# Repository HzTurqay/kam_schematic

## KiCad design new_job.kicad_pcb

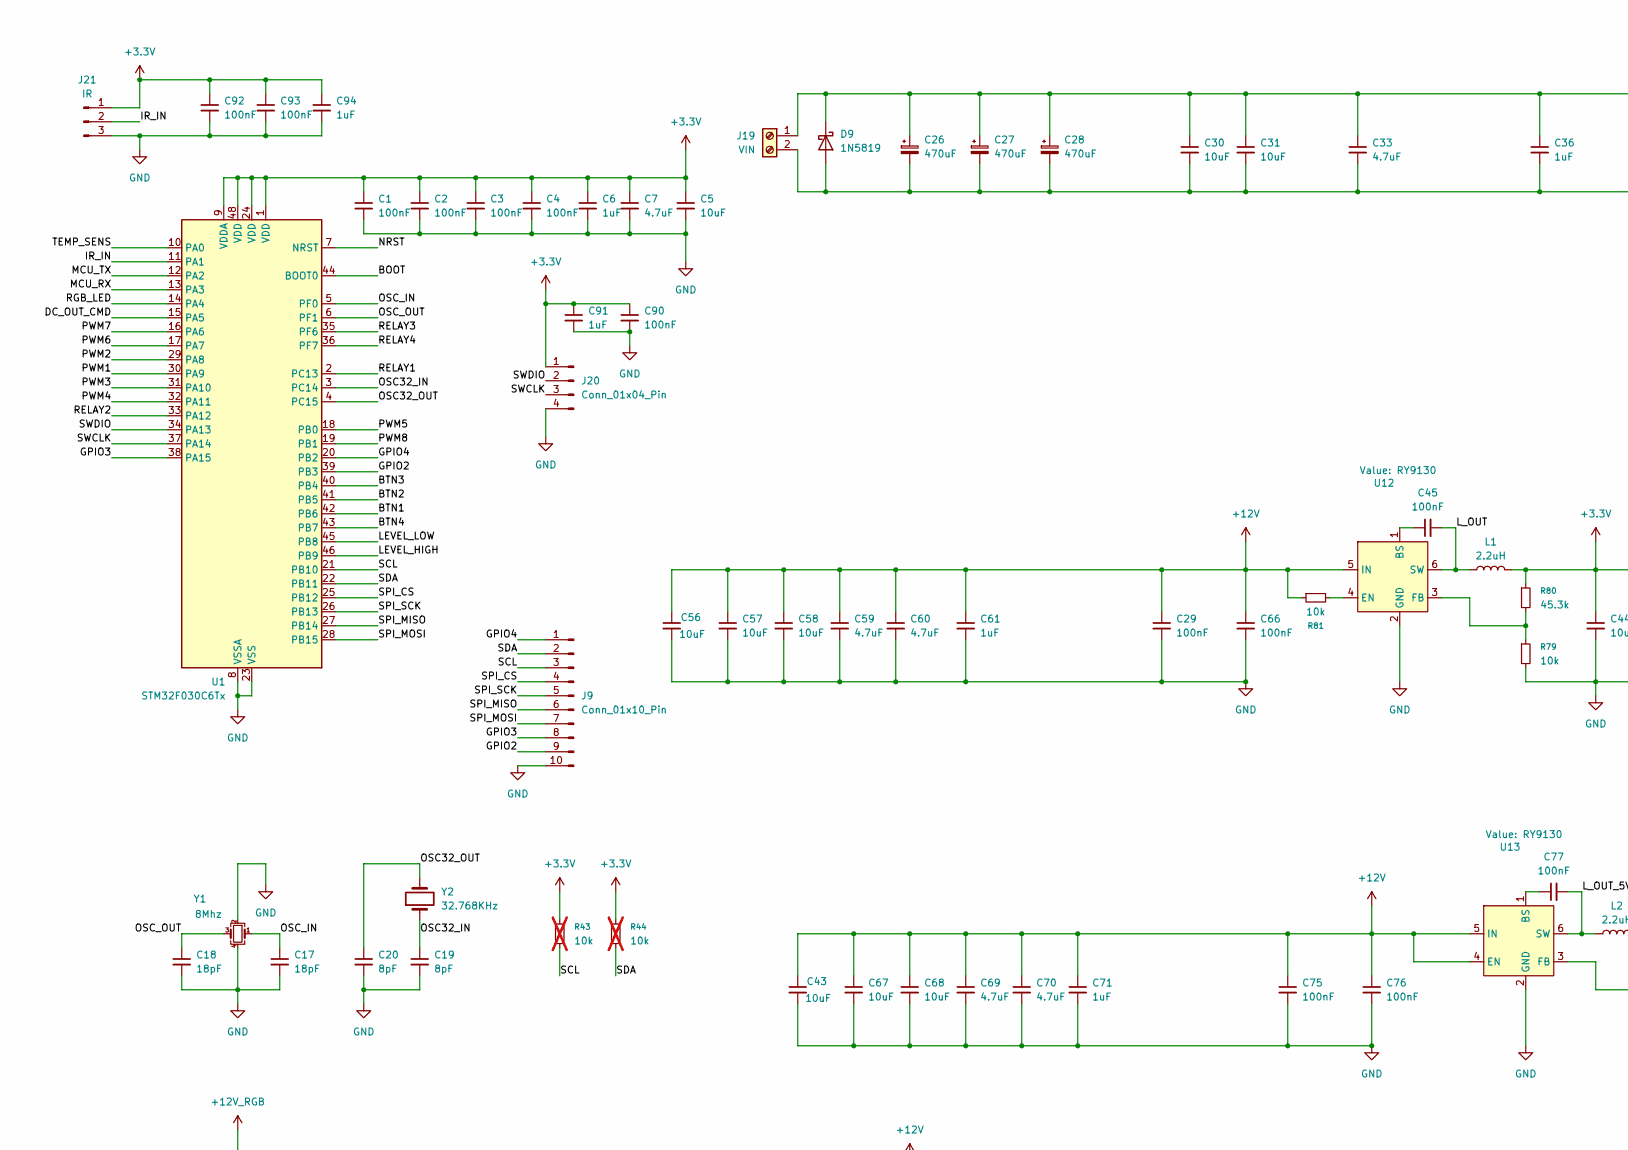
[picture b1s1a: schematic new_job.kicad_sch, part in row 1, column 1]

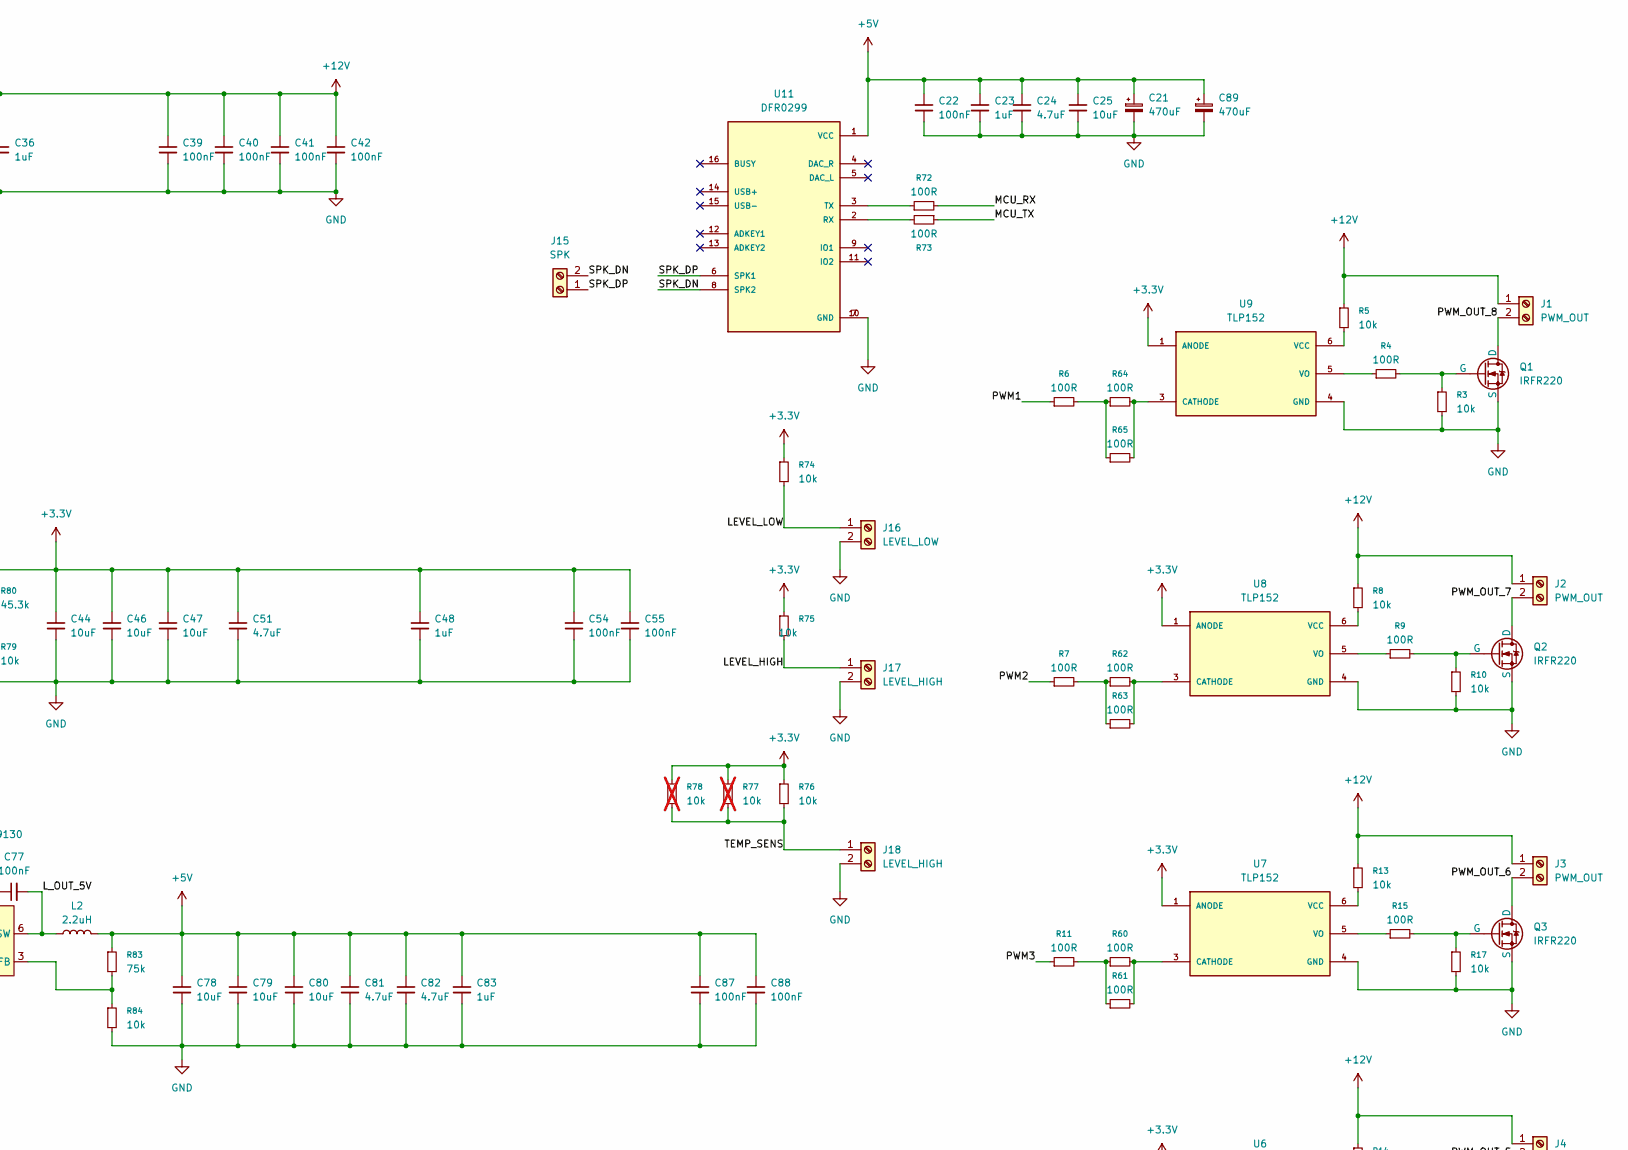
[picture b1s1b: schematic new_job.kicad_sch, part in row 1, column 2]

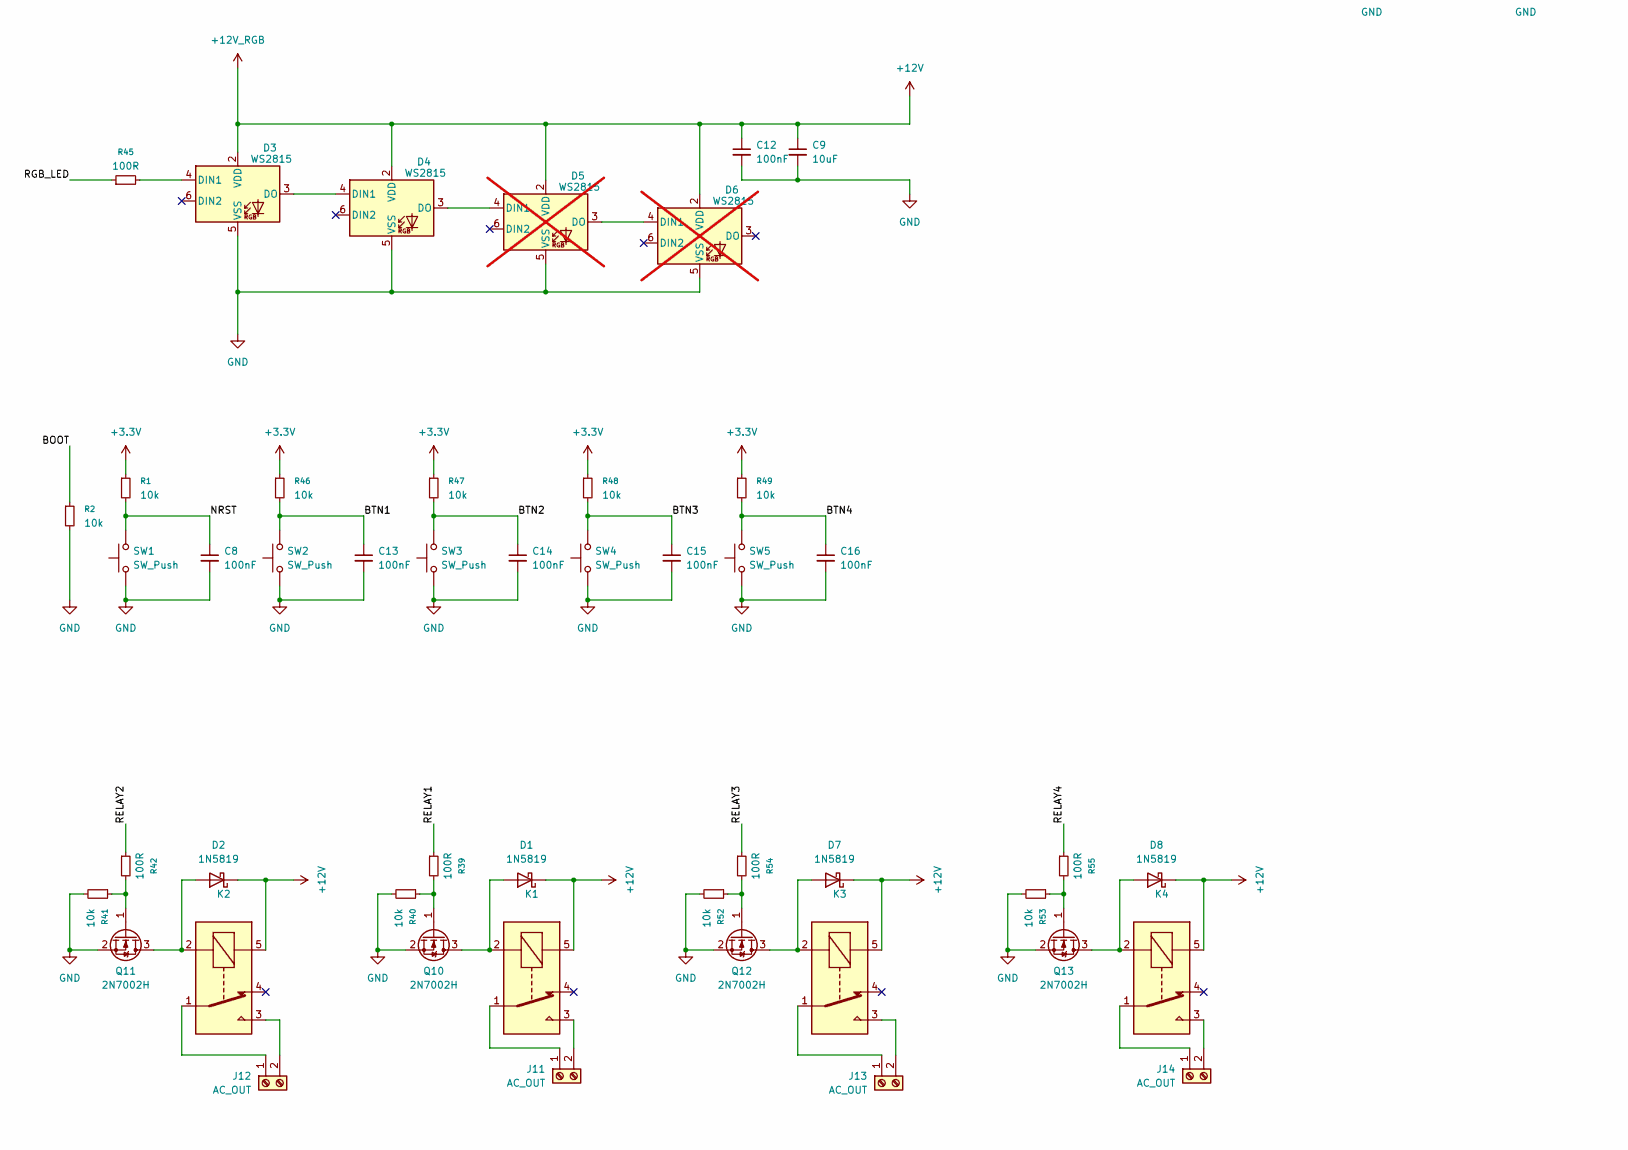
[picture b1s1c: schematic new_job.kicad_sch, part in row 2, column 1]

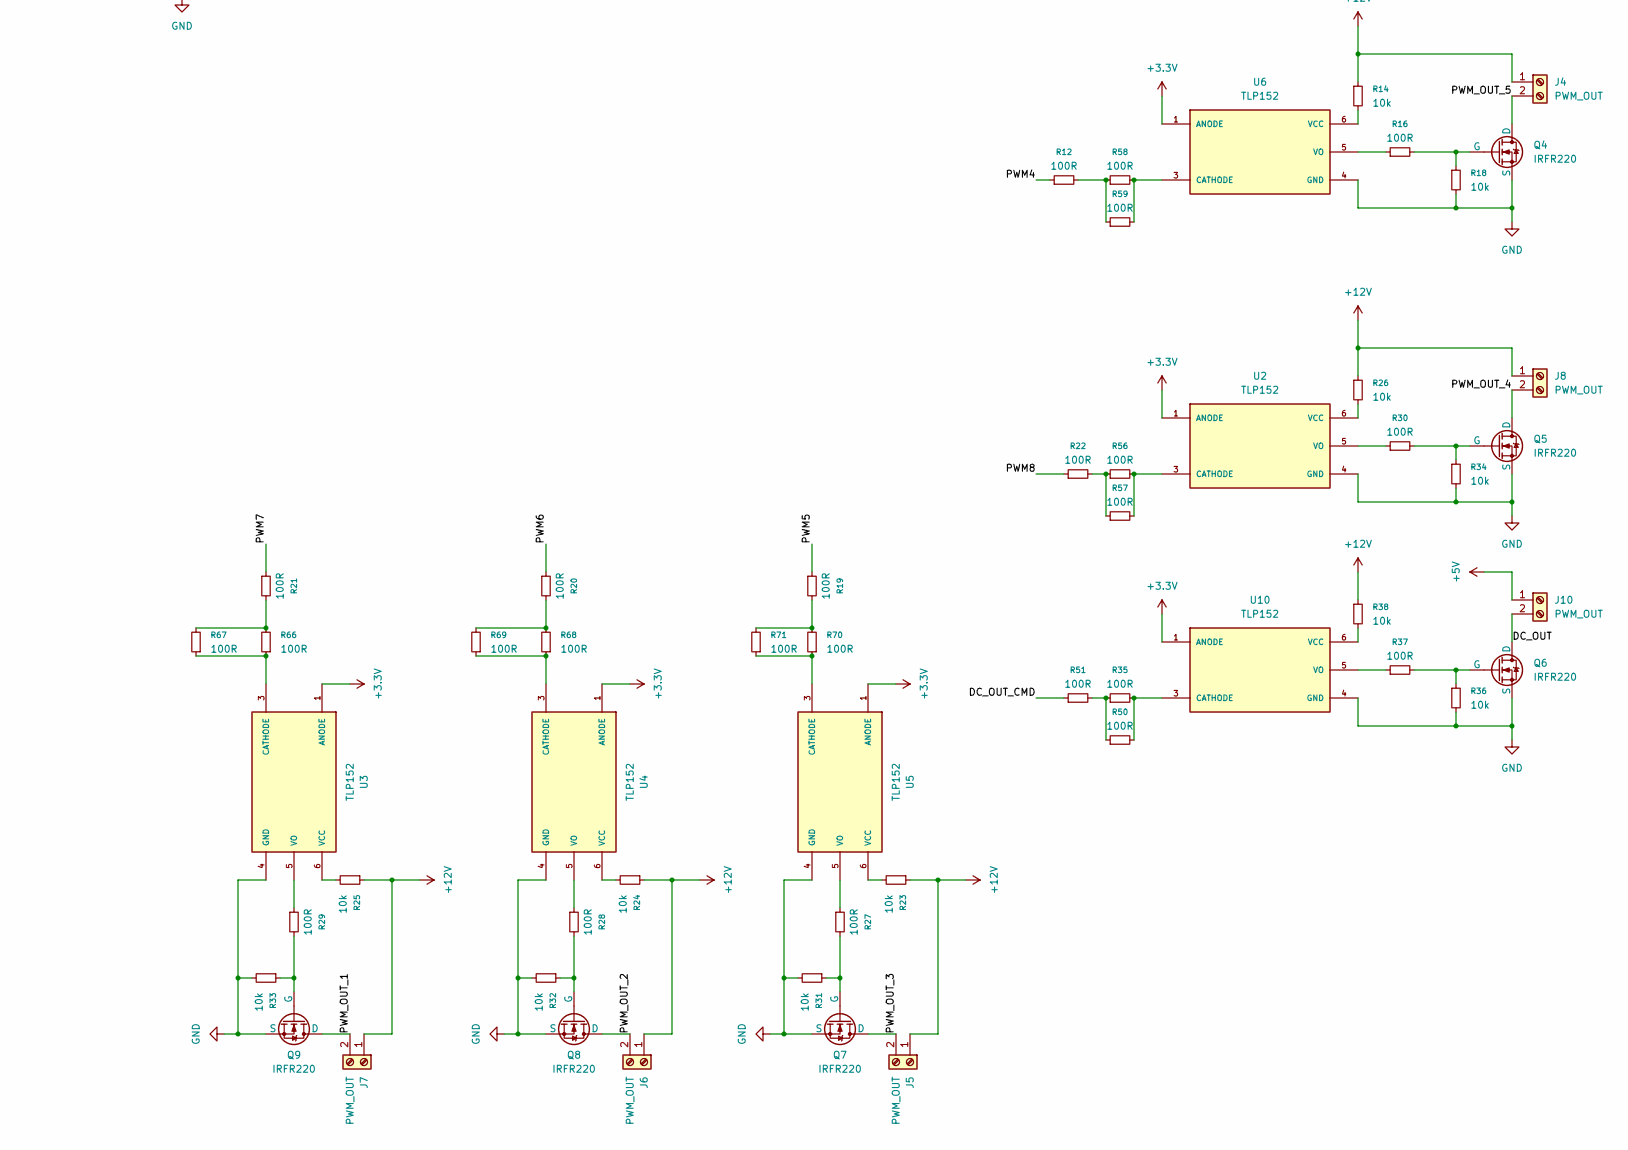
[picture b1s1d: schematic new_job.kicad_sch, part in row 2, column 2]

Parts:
C1, C2, C3, C4, C8, C12, C13, C14, C15, C16, C22, C29, C39, C40, C41, C42, C45, C54, C55, C66, C75, C76, C77, C87, C88, C90, C92, C93: 100nF; C_0402_1005Metric; LCSC Part C328914
C5, C9, C25, C30, C31, C43, C44, C46, C47, C56, C57, C58, C67, C68, C78, C79, C80: 10uF; C_0805_2012Metric; LCSC Part C5137476
C6, C23, C36, C48, C61, C71, C83, C91, C94: 1uF; C_0402_1005Metric; LCSC Part C6119792
C7, C24, C33, C51, C59, C60, C69, C70, C81, C82: 4.7uF; C_0603_1608Metric; LCSC Part C6119855
C17, C18: 18pF; C_0402_1005Metric; LCSC Part C5137554
C19, C20: 8pF; C_0402_1005Metric; LCSC Part C5448809
C21, C26, C27, C28, C89: 470uF; CP_Elec_10x10.5; LCSC Part C5162362
D1, D2, D7, D8, D9: 1N5819; D_SOD-123; LCSC Part C5451628
D3, D4: WS2815; LED_WS2812_PLCC6_5.0x5.0mm_P1.6mm; LCSC Part C19188610
D5, D6: WS2815; LED_WS2812_PLCC6_5.0x5.0mm_P1.6mm; LCSC Part C19188610; not fitted
J1, J2, J3, J4, J5, J6, J7, J8, J10: PWM_OUT; Molex_SL_171971-0002_1x02_P2.54mm_Vertical
J9: Conn_01x10_Pin; PinHeader_1x10_P2.54mm_Vertical
J11, J12, J13, J14: AC_OUT; TerminalBlock_RND_205-00067_1x02_P7.50mm_Horizontal; LCSC Part C557649
J15: SPK; Molex_SL_171971-0002_1x02_P2.54mm_Vertical
J16: LEVEL_LOW; PinHeader_1x02_P2.54mm_Vertical
J17, J18: LEVEL_HIGH; PinHeader_1x02_P2.54mm_Vertical
J19: VIN; Molex_SL_171971-0002_1x02_P2.54mm_Vertical
J20: Conn_01x04_Pin; PinHeader_1x04_P2.54mm_Vertical
J21: IR; PinHeader_1x03_P2.54mm_Vertical
K1, K2, K4: SANYOU_SRD_Form_C; Relay_SPDT_SANYOU_SRD_Series_Form_C; LCSC Part C30431
K3: SANYOU_SRD_Form_C; Relay_SPDT_SANYOU_SRD_Series_Form_C
L1, L2: 2.2uH; L_APV_ANR4010; LCSC Part C431273
Q1, Q2, Q3, Q4, Q5, Q6, Q7, Q8, Q9: IRFR220; TO-252-2; LCSC Part C2584
Q10, Q11, Q12, Q13: 2N7002H; SOT-23; LCSC Part C8545
R1, R2, R3, R5, R8, R10, R13, R14, R17, R18, R23, R24, R25, R26, R31, R32, R33, R34, R36, R38, R40, R41, R46, R47, R48, R49, R52, R53, R74, R75, R76, R79, R81, R84: 10k; R_0402_1005Metric; LCSC Part C881063
R4, R6, R7, R9, R11, R12, R15, R16, R19, R20, R21, R22, R27, R28, R29, R30, R35, R37, R39, R42, R45, R50, R51, R54, R55, R56, R57, R58, R59, R60, R61, R62, R63, R64, R65, R66, R67, R68, R69, R70, R71, R72, R73: 100R; R_0402_1005Metric; LCSC Part C22369194
R43, R44, R77, R78: 10k; R_0402_1005Metric; LCSC Part C881063; not fitted
R80: 45.3k; R_0402_1005Metric; LCSC Part C2933099
R83: 75k; R_0402_1005Metric; LCSC Part C2906965
SW1, SW2, SW3, SW4, SW5: SW_Push; SW_SPST_B3S-1000; LCSC Part C2909692
U1: STM32F030C6Tx; LQFP-48_7x7mm_P0.5mm; LCSC Part C106925
U2, U3, U4, U5, U6, U7, U8, U9, U10: TLP152; IC_TLP152; PARTREV 6; LCSC Part C22436730
U11: DFR0299; MODULE_DFR0299
U12, U13: RY9130; SOT-23-6; LCSC Part C2981046
Y1: 8Mhz; Crystal_SMD_3225-4Pin_3.2x2.5mm; LCSC Part C2835958
Y2: 32.768KHz; Crystal_SMD_3215-2Pin_3.2x1.5mm; LCSC Part C907541

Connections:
+3.3V: C1.1, C2.1, C3.1, C4.1, C5.1, C6.1, C7.1, C44.1, C46.1, C47.1, C48.1, C51.1, C54.1, C55.1, C90.1, C91.1, C92.1, C93.1, C94.1, J20.1, J21.1, L1.2, R1.1, R43.1, R44.1, R46.1, R47.1, R48.1, R49.1, R74.1, R75.1, R76.1, R77.1, R78.1, R80.1, U1.1 (VDD), U1.9 (VDDA), U1.24 (VDD), U1.48 (VDD), U2.1 (ANODE), U3.1 (ANODE), U4.1 (ANODE), U5.1 (ANODE), U6.1 (ANODE), U7.1 (ANODE), U8.1 (ANODE), U9.1 (ANODE), U10.1 (ANODE)
+5V: C21.1, C22.1, C23.1, C24.1, C25.1, C78.1, C79.1, C80.1, C81.1, C82.1, C83.1, C87.1, C88.1, C89.1, J10.1, L2.2, R83.1, U11.1 (VCC)
+12V: C9.1, C12.1, C26.1, C27.1, C28.1, C29.1, C30.1, C31.1, C33.1, C36.1, C39.1, C40.1, C41.1, C42.1, C43.1, C56.1, C57.1, C58.1, C59.1, C60.1, C61.1, C66.1, C67.1, C68.1, C69.1, C70.1, C71.1, C75.1, C76.1, D1.1 (K), D2.1 (K), D3.2 (VDD), D4.2 (VDD), D5.2 (VDD), D6.2 (VDD), D7.1 (K), D8.1 (K), D9.1 (K), J1.1, J2.1, J3.1, J4.1, J5.1, J6.1, J7.1, J8.1, J19.1, K1.5, K2.5, K3.5, K4.5, R5.1, R8.1, R13.1, R14.1, R23.1, R24.1, R25.1, R26.1, R38.1, R81.1, U12.5 (IN), U13.4 (EN), U13.5 (IN)
/BOOT: R2.1, U1.44 (BOOT0)
/BTN1: C13.1, R46.2, SW2.2, U1.42 (PB6)
/BTN2: C14.1, R47.2, SW3.2, U1.41 (PB5)
/BTN3: C15.1, R48.2, SW4.2, U1.40 (PB4)
/BTN4: C16.1, R49.2, SW5.2, U1.43 (PB7)
/DC_OUT: J10.2, Q6.2 (D)
/DC_OUT_CMD: R51.1, U1.15 (PA5)
/GPIO2: J9.9, U1.39 (PB3)
/GPIO3: J9.8, U1.38 (PA15)
/GPIO4: J9.1, U1.20 (PB2)
/IR_IN: J21.2, U1.11 (PA1)
/LEVEL_HIGH: J17.1, R75.2, U1.46 (PB9)
/LEVEL_LOW: J16.1, R74.2, U1.45 (PB8)
/L_OUT: C45.2, L1.1, U12.6 (SW)
/L_OUT_5V: C77.2, L2.1, U13.6 (SW)
/MCU_RX: R72.2, U1.13 (PA3)
/MCU_TX: R73.1, U1.12 (PA2)
/NRST: C8.1, R1.2, SW1.2, U1.7 (NRST)
/OSC32_IN: C19.1, U1.3 (PC14), Y2.1
/OSC32_OUT: C20.1, U1.4 (PC15), Y2.2
/OSC_IN: C17.1, U1.5 (PF0), Y1.1
/OSC_OUT: C18.1, U1.6 (PF1), Y1.3
/PWM1: R6.1, U1.30 (PA9)
/PWM2: R7.1, U1.29 (PA8)
/PWM3: R11.1, U1.31 (PA10)
/PWM4: R12.1, U1.32 (PA11)
/PWM5: R19.1, U1.18 (PB0)
/PWM6: R20.1, U1.17 (PA7)
/PWM7: R21.1, U1.16 (PA6)
/PWM8: R22.1, U1.19 (PB1)
/PWM_OUT_1: J7.2, Q9.2 (D)
/PWM_OUT_2: J6.2, Q8.2 (D)
/PWM_OUT_3: J5.2, Q7.2 (D)
/PWM_OUT_4: J8.2, Q5.2 (D)
/PWM_OUT_5: J4.2, Q4.2 (D)
/PWM_OUT_6: J3.2, Q3.2 (D)
/PWM_OUT_7: J2.2, Q2.2 (D)
/PWM_OUT_8: J1.2, Q1.2 (D)
/RELAY1: R39.1, U1.2 (PC13)
/RELAY2: R42.1, U1.33 (PA12)
/RELAY3: R54.1, U1.35 (PF6)
/RELAY4: R55.1, U1.36 (PF7)
/RGB_LED: R45.1, U1.14 (PA4)
/SCL: J9.3, R43.2, U1.21 (PB10)
/SDA: J9.2, R44.2, U1.22 (PB11)
/SPI_CS: J9.4, U1.25 (PB12)
/SPI_MISO: J9.6, U1.27 (PB14)
/SPI_MOSI: J9.7, U1.28 (PB15)
/SPI_SCK: J9.5, U1.26 (PB13)
/SPK_DN: J15.2, U11.8 (SPK2)
/SPK_DP: J15.1, U11.6 (SPK1)
/SWCLK: J20.3, U1.37 (PA14)
/SWDIO: J20.2, U1.34 (PA13)
/TEMP_SENS: J18.1, R76.2, R77.2, R78.2, U1.10 (PA0)
GND: C1.2, C2.2, C3.2, C4.2, C5.2, C6.2, C7.2, C8.2, C9.2, C12.2, C13.2, C14.2, C15.2, C16.2, C17.2, C18.2, C19.2, C20.2, C21.2, C22.2, C23.2, C24.2, C25.2, C26.2, C27.2, C28.2, C29.2, C30.2, C31.2, C33.2, C36.2, C39.2, C40.2, C41.2, C42.2, C43.2, C44.2, C46.2, C47.2, C48.2, C51.2, C54.2, C55.2, C56.2, C57.2, C58.2, C59.2, C60.2, C61.2, C66.2, C67.2, C68.2, C69.2, C70.2, C71.2, C75.2, C76.2, C78.2, C79.2, C80.2, C81.2, C82.2, C83.2, C87.2, C88.2, C89.2, C90.2, C91.2, C92.2, C93.2, C94.2, D3.5 (VSS), D4.5 (VSS), D5.5 (VSS), D6.5 (VSS), D9.2 (A), J9.10, J16.2, J17.2, J18.2, J19.2, J20.4, J21.3, Q1.3 (S), Q2.3 (S), Q3.3 (S), Q4.3 (S), Q5.3 (S), Q6.3 (S), Q7.3 (S), Q8.3 (S), Q9.3 (S), Q10.2 (S), Q11.2 (S), Q12.2 (S), Q13.2 (S), R2.2, R3.2, R10.2, R17.2, R18.2, R31.2, R32.2, R33.2, R34.2, R36.2, R40.2, R41.2, R52.2, R53.2, R79.2, R84.2, SW1.1, SW2.1, SW3.1, SW4.1, SW5.1, U1.8 (VSSA), U1.23 (VSS), U1.47 (VSS), U2.4 (GND), U3.4 (GND), U4.4 (GND), U5.4 (GND), U6.4 (GND), U7.4 (GND), U8.4 (GND), U9.4 (GND), U10.4 (GND), U11.7 (GND), U11.10 (GND), U12.2 (GND), U13.2 (GND), Y1.2, Y1.4
unnamed: D1.2 (A), K1.2, Q10.3 (D)
unnamed: D2.2 (A), K2.2, Q11.3 (D)
unnamed: D3.4 (DIN1), R45.2
unnamed: D3.3 (DO), D4.4 (DIN1)
unnamed: D4.3 (DO), D5.4 (DIN1)
unnamed: D5.3 (DO), D6.4 (DIN1)
unnamed: D7.2 (A), K3.2, Q12.3 (D)
unnamed: D8.2 (A), K4.2, Q13.3 (D)
unnamed: J11.1, K1.1
unnamed: J11.2, K1.3
unnamed: J12.1, K2.1
unnamed: J12.2, K2.3
unnamed: J13.1, K3.1
unnamed: J13.2, K3.3
unnamed: J14.1, K4.1
unnamed: J14.2, K4.3
unnamed: Q1.1 (G), R3.1, R4.2
unnamed: Q2.1 (G), R9.2, R10.1
unnamed: Q3.1 (G), R15.2, R17.1
unnamed: Q4.1 (G), R16.2, R18.1
unnamed: Q5.1 (G), R30.2, R34.1
unnamed: Q6.1 (G), R36.1, R37.2
unnamed: Q7.1 (G), R27.2, R31.1
unnamed: Q8.1 (G), R28.2, R32.1
unnamed: Q9.1 (G), R29.2, R33.1
unnamed: Q10.1 (G), R39.2, R40.1
unnamed: Q11.1 (G), R41.1, R42.2
unnamed: Q12.1 (G), R52.1, R54.2
unnamed: Q13.1 (G), R53.1, R55.2
unnamed: R6.2, R64.1, R65.1
unnamed: R11.2, R60.1, R61.1
unnamed: R12.2, R58.1, R59.1
unnamed: R19.2, R70.2, R71.2
unnamed: R20.2, R68.2, R69.2
unnamed: R21.2, R66.2, R67.2
unnamed: R22.2, R56.1, R57.1
unnamed: R35.1, R50.1, R51.2
unnamed: R7.2, R62.1, R63.1
unnamed: R56.2, R57.2, U2.3 (CATHODE)
unnamed: R26.2, U2.6 (VCC)
unnamed: R30.1, U2.5 (VO)
unnamed: R66.1, R67.1, U3.3 (CATHODE)
unnamed: R25.2, U3.6 (VCC)
unnamed: R29.1, U3.5 (VO)
unnamed: R68.1, R69.1, U4.3 (CATHODE)
unnamed: R24.2, U4.6 (VCC)
unnamed: R28.1, U4.5 (VO)
unnamed: R70.1, R71.1, U5.3 (CATHODE)
unnamed: R23.2, U5.6 (VCC)
unnamed: R27.1, U5.5 (VO)
unnamed: R58.2, R59.2, U6.3 (CATHODE)
unnamed: R14.2, U6.6 (VCC)
unnamed: R16.1, U6.5 (VO)
unnamed: R60.2, R61.2, U7.3 (CATHODE)
unnamed: R13.2, U7.6 (VCC)
unnamed: R15.1, U7.5 (VO)
unnamed: R62.2, R63.2, U8.3 (CATHODE)
unnamed: R8.2, U8.6 (VCC)
unnamed: R9.1, U8.5 (VO)
unnamed: R64.2, R65.2, U9.3 (CATHODE)
unnamed: R5.2, U9.6 (VCC)
unnamed: R4.1, U9.5 (VO)
unnamed: R35.2, R50.2, U10.3 (CATHODE)
unnamed: R38.2, U10.6 (VCC)
unnamed: R37.1, U10.5 (VO)
unnamed: R73.2, U11.2 (RX)
unnamed: R72.1, U11.3 (TX)
unnamed: C45.1, U12.1 (BS)
unnamed: R81.2, U12.4 (EN)
unnamed: R79.1, R80.2, U12.3 (FB)
unnamed: C77.1, U13.1 (BS)
unnamed: R83.2, R84.1, U13.3 (FB)

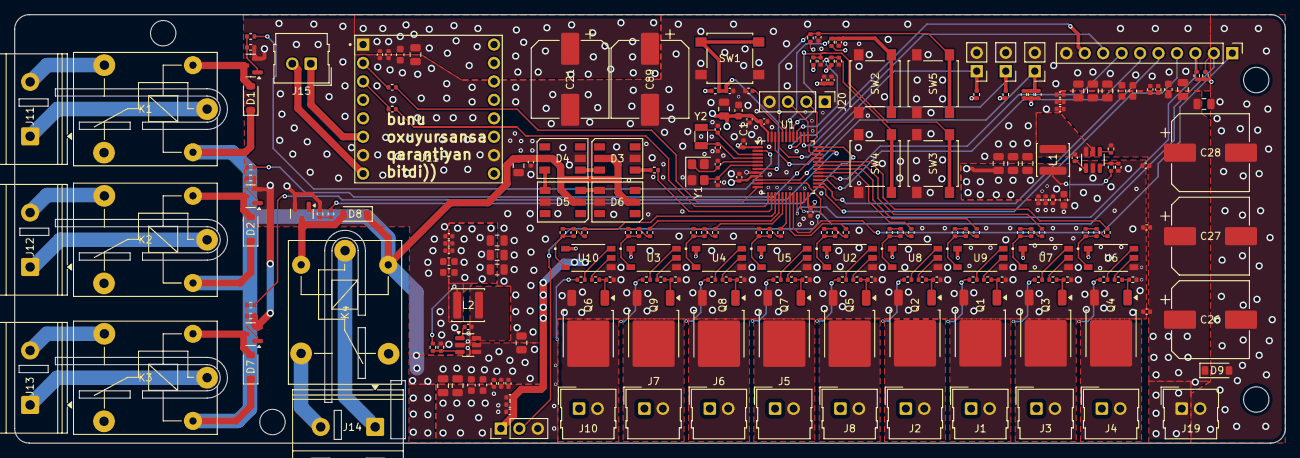
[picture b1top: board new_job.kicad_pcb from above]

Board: 4 copper layers, 175.0 x 59.0 mm, 225 parts (0 on the bottom side), 130 nets.

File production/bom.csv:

Designator,Footprint,Quantity,Value,LCSC Part #
C1, C12, C13, C14, C15, C16, C2, C22, C29, C3, C39, C4, C40, C41, C42, C45, C54, C55, C66, C75, C76, C77, C8, C87, C88, C90, C92, C93,0402,28,100nF,C328914
C17, C18,0402,2,18pF,C5137554
C19, C20,0402,2,8pF,C5448809
C21, C26, C27, C28, C89,CP_Elec_10x10.5,5,470uF,C5162362
C23, C36, C48, C6, C61, C71, C83, C91, C94,0402,9,1uF,C6119792
C24, C33, C51, C59, C60, C69, C7, C70, C81, C82,0603,10,4.7uF,C6119855
C25, C30, C31, C43, C44, C46, C47, C5, C56, C57, C58, C67, C68, C78, C79, C80, C9,0805,17,10uF,C5137476
D1, D2, D7, D8, D9,D_SOD-123,5,1N5819,C5451628
D3, D4, D5, D6,LED_WS2812_PLCC6_5.0x5.0mm_P1.6mm,4,WS2815,C19188610
J1, J10, J2, J3, J4, J5, J6, J7, J8,Molex_SL_171971-0002_1x02_P2.54mm_Vertical,9,PWM_OUT,
J11, J12, J13, J14,TerminalBlock_RND_205-00067_1x02_P7.50mm_Horizontal,4,AC_OUT,C557649
J15,Molex_SL_171971-0002_1x02_P2.54mm_Vertical,1,SPK,
J16,PinHeader_1x02_P2.54mm_Vertical,1,LEVEL_LOW,
J17, J18,PinHeader_1x02_P2.54mm_Vertical,2,LEVEL_HIGH,
J19,Molex_SL_171971-0002_1x02_P2.54mm_Vertical,1,VIN,
J20,PinHeader_1x04_P2.54mm_Vertical,1,Conn_01x04_Pin,
J21,PinHeader_1x03_P2.54mm_Vertical,1,IR,
J9,PinHeader_1x10_P2.54mm_Vertical,1,Conn_01x10_Pin,
K1, K2, K4,Relay_SPDT_SANYOU_SRD_Series_Form_C,3,SANYOU_SRD_Form_C,C30431
K3,Relay_SPDT_SANYOU_SRD_Series_Form_C,1,SANYOU_SRD_Form_C,
L1, L2,L_APV_ANR4010,2,2.2uH,C431273
Q1, Q2, Q3, Q4, Q5, Q6, Q7, Q8, Q9,TO-252-2,9,IRFR220,C2584
Q10, Q11, Q12, Q13,SOT-23,4,2N7002H,C8545
R1, R10, R13, R14, R17, R18, R2, R23, R24, R25, R26, R3, R31, R32, R33, R34, R36, R38, R40, R41, R43, R44, R46, R47, R48, R49, R5, R52, R53, R74, R75, R76, R77, R78, R79, R8, R81, R84,0402,38,10k,C881063
R11, R12, R15, R16, R19, R20, R21, R22, R27, R28, R29, R30, R35, R37, R39, R4, R42, R45, R50, R51, R54, R55, R56, R57, R58, R59, R6, R60, R61, R62, R63, R64, R65, R66, R67, R68, R69, R7, R70, R71, R72, R73, R9,0402,43,100R,C22369194
R80,0402,1,45.3k,C2933099
R83,0402,1,75k,C2906965
SW1, SW2, SW3, SW4, SW5,SW_SPST_B3S-1000,5,SW_Push,C2909692
U1,LQFP-48_7x7mm_P0.5mm,1,STM32F030C6Tx,C106925
U10, U2, U3, U4, U5, U6, U7, U8, U9,IC_TLP152,9,TLP152,C22436730
U11,MODULE_DFR0299,1,DFR0299,
U12, U13,SOT-23-6,2,RY9130,C2981046
Y1,Crystal_SMD_3225-4Pin_3.2x2.5mm,1,8Mhz,C2835958
Y2,Crystal_SMD_3215-2Pin_3.2x1.5mm,1,32.768KHz,C907541

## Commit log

2025-08-26 Initial schematic
2025-08-27 crystals added
2025-08-28 pcb started
2025-08-29 PCB improoved
2025-09-03 production ready
